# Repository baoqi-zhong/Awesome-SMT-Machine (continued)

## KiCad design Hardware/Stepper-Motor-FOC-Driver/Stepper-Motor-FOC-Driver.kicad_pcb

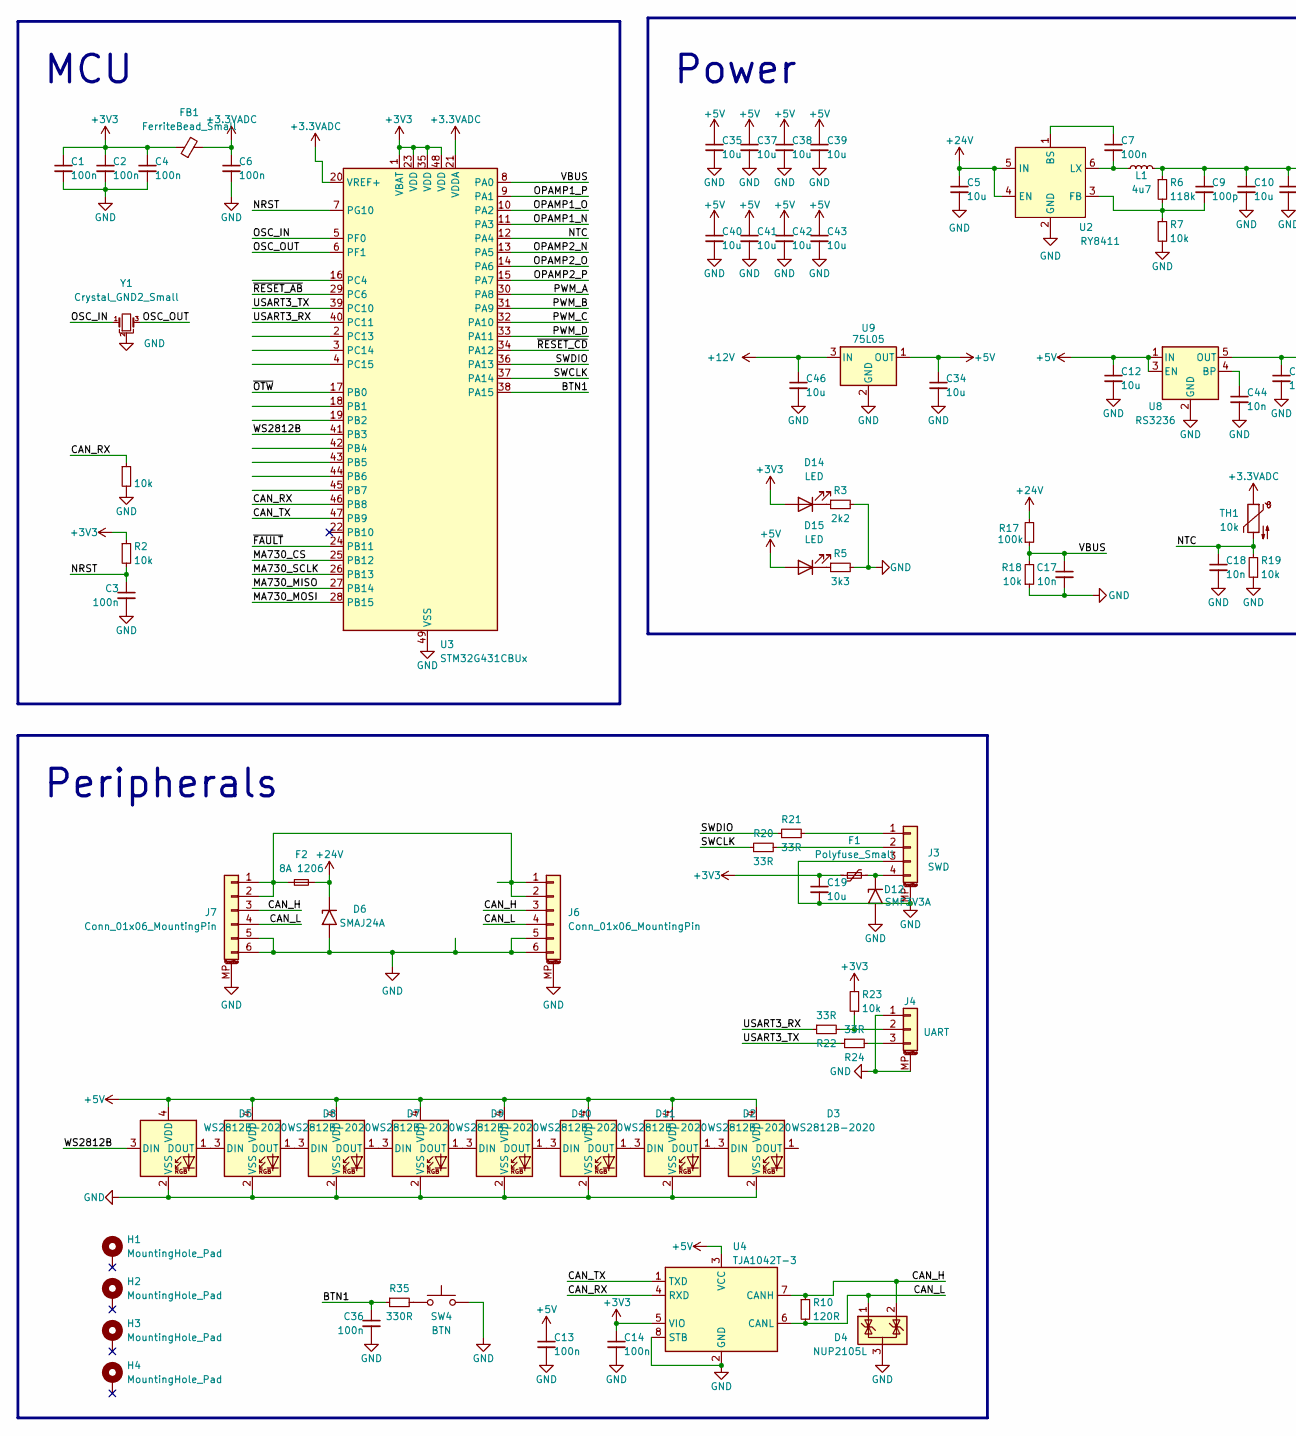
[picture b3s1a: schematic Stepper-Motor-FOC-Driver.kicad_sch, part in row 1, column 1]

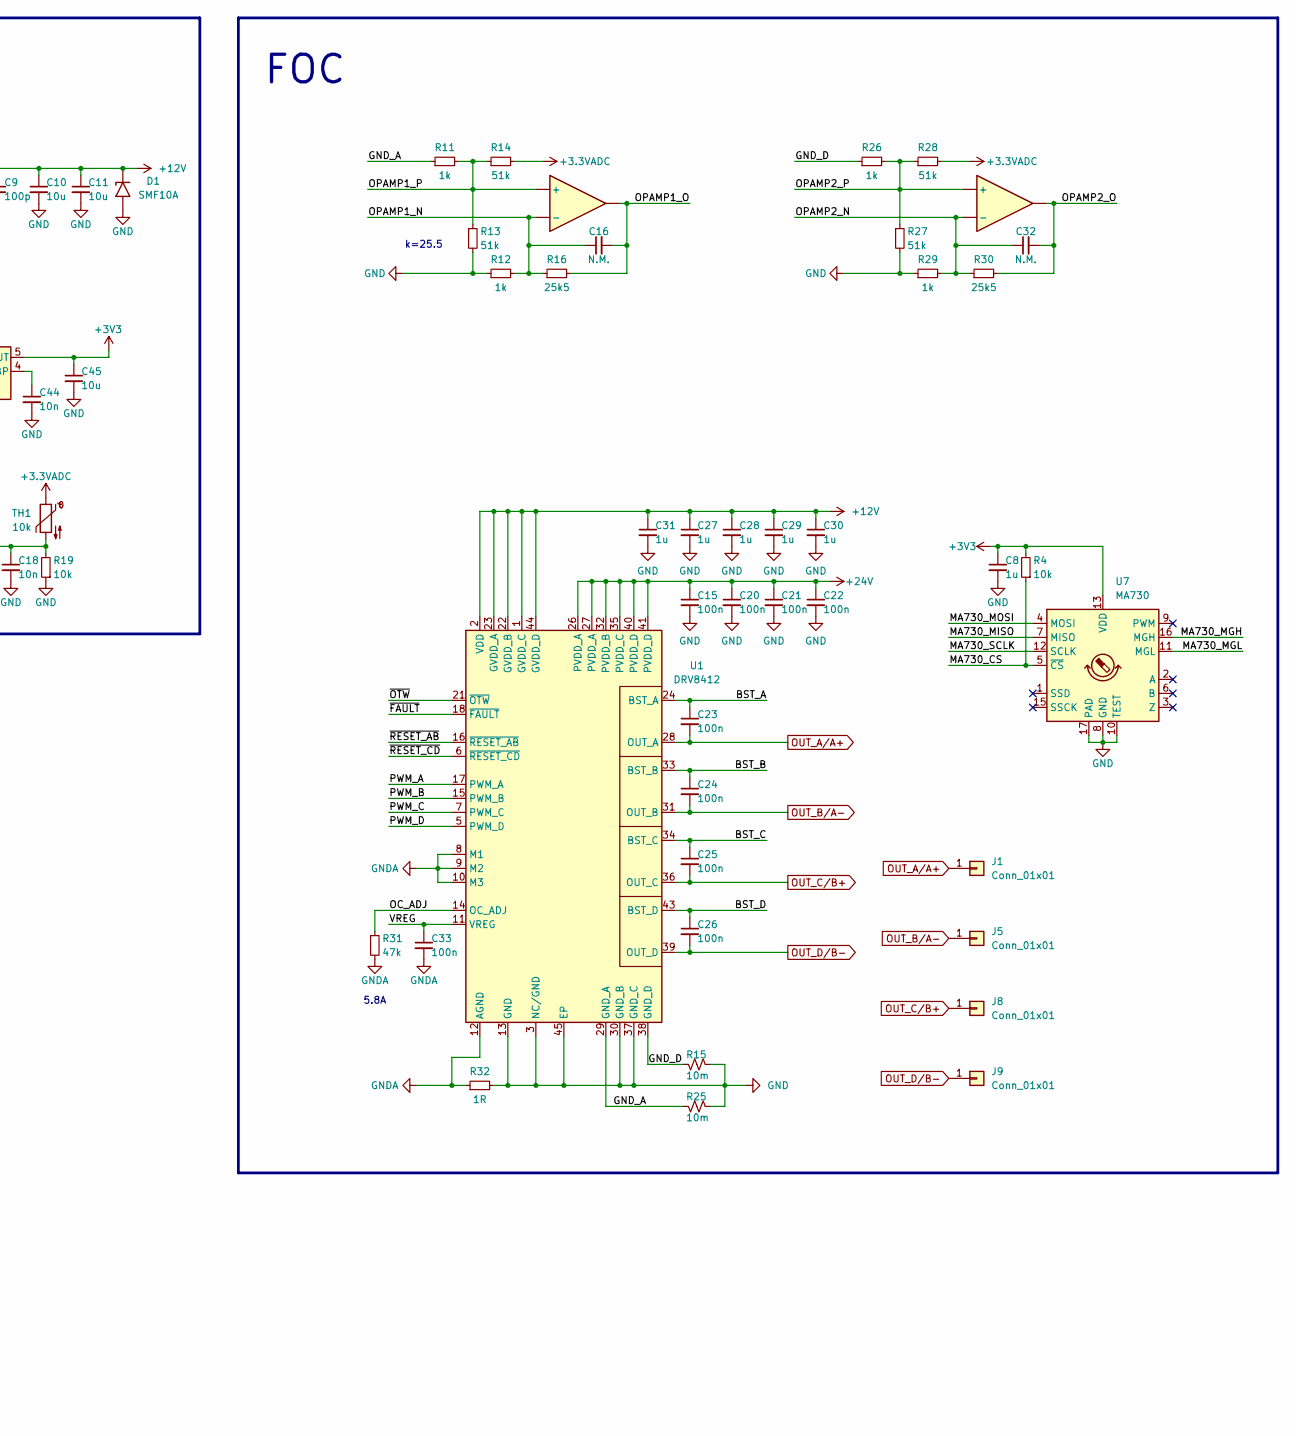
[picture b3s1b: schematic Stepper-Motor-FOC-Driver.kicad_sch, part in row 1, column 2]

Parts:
C1, C2, C3, C4, C6, C7, C13, C14, C15, C20, C21, C22, C23, C24, C25, C26, C33, C36: 100n; C_0603_1608Metric
C5, C10, C11: 10u; C_1206_3216Metric
C8, C27, C28, C29, C30, C31: 1u; C_0603_1608Metric
C9: 100p; C_0603_1608Metric
C12, C19, C34, C35, C37, C38, C39, C40, C41, C42, C43, C45, C46: 10u; C_0603_1608Metric
C16, C32: N.M.; C_0603_1608Metric
C17, C18, C44: 10n; C_0603_1608Metric
D1: SMF10A; D_SMF
D2, D3, D5, D7, D8, D9, D10, D11: WS2812B-2020; LED_WS2812B-2020_PLCC4_2.0x2.0mm
D4: NUP2105L; SOT-23
D6: SMAJ24A; D_SMA
D12: SMF3V3A; D_SMF
D14, D15: LED; LED_0603_1608Metric
F1: Polyfuse_Small; Fuse_1206_3216Metric
F2: 8A 1206; Fuse_1206_3216Metric
FB1: FerriteBead_Small; L_0603_1608Metric
H1, H2, H3, H4: MountingHole_Pad; MountingHole_3.2mm_M3_DIN965_Pad
J1, J5, J8, J9: Conn_01x01; TestPoint_Pad_3.0x3.0mm
J3: SWD; Molex_PicoBlade_53047-0410_1x04_P1.25mm_Vertical
J4: UART; JST_GH_SM03B-GHS-TB_1x03-1MP_P1.25mm_Horizontal
J6, J7: Conn_01x06_MountingPin; JST_PH_S6B-PH-K_1x06_P2.00mm_Horizontal
L1: 4u7; L_Sunlord_MWSA0402S
R1, R2, R4, R7, R18, R19, R23: 10k; R_0603_1608Metric
R3: 2k2; R_0603_1608Metric
R5: 3k3; R_0603_1608Metric
R6: 118k; R_0603_1608Metric
R10: 120R; R_0603_1608Metric
R11, R12, R26, R29: 1k; R_0603_1608Metric
R13, R14, R27, R28: 51k; R_0603_1608Metric
R15, R25: 10m; R_1206_3216Metric
R16, R30: 25k5; R_0603_1608Metric
R17: 100k; R_0603_1608Metric
R20, R21, R22, R24: 33R; R_0603_1608Metric
R31: 47k; R_0603_1608Metric
R32: 1R; R_0603_1608Metric
R35: 330R; R_0603_1608Metric
SW4: BTN; SW_SPST_PTS810
TH1: 10k; TestPoint_2Pads_Pitch2.54mm_Drill0.8mm
U1: DRV8412; HTSSOP-44-1EP_6.1x14mm_P0.635mm_EP5.2x14mm_Mask4.31x8.26mm
U2: RY8411; SOT-23-6
U3: STM32G431CBUx; QFN-48-1EP_7x7mm_P0.5mm_EP5.6x5.6mm
U4: TJA1042T-3; SOIC-8_3.9x4.9mm_P1.27mm
U5, U6: type="X" model="OPAMP" lib=""
U7: MA730; QFN-16-1EP_3x3mm_P0.5mm_EP1.75x1.75mm
U8: RS3236; SOT-23-5
U9: 75L05; SOT-89-3
Y1: Crystal_GND2_Small; Resonator_SMD_Murata_CSTxExxV-3Pin_3.0x1.1mm

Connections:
+3.3VADC: C6.1, FB1.2, R14.2, R28.2, TH1.1, U3.20 (VREF+), U3.21 (VDDA)
+3V3: C1.1, C2.1, C4.1, C8.1, C14.1, C19.1, C45.1, D14.2 (A), F1.1, FB1.1, R2.1, R4.2, R23.2, U3.1 (VBAT), U3.23 (VDD), U3.35 (VDD), U3.48 (VDD), U4.5 (VIO), U7.13 (VDD), U8.5 (OUT)
+5V: C12.1, C13.1, C34.1, C35.1, C37.1, C38.1, C39.1, C40.1, C41.1, C42.1, C43.1, D2.4 (VDD), D3.4 (VDD), D5.4 (VDD), D7.4 (VDD), D8.4 (VDD), D9.4 (VDD), D10.4 (VDD), D11.4 (VDD), D15.2 (A), U4.3 (VCC), U8.1 (IN), U8.3 (EN), U9.1 (OUT)
+12V: C9.1, C10.1, C11.1, C27.1, C28.1, C29.1, C30.1, C31.1, C46.1, D1.1 (A1), L1.2, R6.1, U1.1 (GVDD_C), U1.2 (VDD), U1.22 (GVDD_B), U1.23 (GVDD_A), U1.44 (GVDD_D), U9.3 (IN)
+24V: C5.1, C15.1, C20.1, C21.1, C22.1, D6.1 (A1), F2.2, R17.2, U1.26 (PVDD_A), U1.27 (PVDD_A), U1.32 (PVDD_B), U1.35 (PVDD_C), U1.40 (PVDD_D), U1.41 (PVDD_D), U2.4 (EN), U2.5 (IN)
/BST_A: C23.1, U1.24 (BST_A)
/BST_B: C24.1, U1.33 (BST_B)
/BST_C: C25.1, U1.34 (BST_C)
/BST_D: C26.1, U1.43 (BST_D)
/BTN1: C36.1, R35.1, U3.38 (PA15)
/CAN_H: D4.2 (K), J6.3, J7.3, R10.1, U4.7 (CANH)
/CAN_L: D4.1 (K), J6.4, J7.4, R10.2, U4.6 (CANL)
/CAN_RX: R1.1, U3.46 (PB8), U4.4 (RXD)
/CAN_TX: U3.47 (PB9), U4.1 (TXD)
/GND_A: R11.1, R25.2, U1.29 (GND_A)
/GND_D: R15.2, R26.1, U1.38 (GND_D)
/MA730_CS: R4.1, U3.25 (PB12), U7.5 (~CS)
/MA730_MGH: U7.16 (MGH)
/MA730_MGL: U7.11 (MGL)
/MA730_MISO: U3.27 (PB14), U7.7 (MISO)
/MA730_MOSI: U3.28 (PB15), U7.4 (MOSI)
/MA730_SCLK: U3.26 (PB13), U7.12 (SCLK)
/NRST: C3.1, R2.2, U3.7 (PG10)
/NTC: C18.1, R19.2, TH1.2, U3.12 (PA4)
/OC_ADJ: R31.1, U1.14 (OC_ADJ)
/OPAMP1_N: C16.1, R12.2, R16.1, U3.11 (PA3), U5.
/OPAMP1_O: C16.2, R16.2, U3.10 (PA2), U5.
/OPAMP1_P: R11.2, R13.1, R14.1, U3.9 (PA1), U5.
/OPAMP2_N: C32.1, R29.2, R30.1, U3.13 (PA5), U6.
/OPAMP2_O: C32.2, R30.2, U3.14 (PA6), U6.
/OPAMP2_P: R26.2, R27.1, R28.1, U3.15 (PA7), U6.
/OSC_IN: U3.5 (PF0), Y1.1
/OSC_OUT: U3.6 (PF1), Y1.3
/PWM_A: U1.17 (PWM_A), U3.30 (PA8)
/PWM_B: U1.15 (PWM_B), U3.31 (PA9)
/PWM_C: U1.7 (PWM_C), U3.32 (PA10)
/PWM_D: U1.5 (PWM_D), U3.33 (PA11)
/SWCLK: R20.1, U3.37 (PA14)
/SWDIO: R21.1, U3.36 (PA13)
/USART3_RX: R22.1, U3.40 (PC11)
/USART3_TX: R24.1, U3.39 (PC10)
/VBUS: C17.1, R17.1, R18.2, U3.8 (PA0)
/VREG: C33.1, U1.11 (VREG)
/WS2812B: D5.3 (DIN), U3.41 (PB3)
/~FAULT: U1.18 (~FAULT), U3.24 (PB11)
/~OTW: U1.21 (~OTW), U3.17 (PB0)
/~RESET_AB: U1.16 (~RESET_AB), U3.29 (PC6)
/~RESET_CD: U1.6 (~RESET_CD), U3.34 (PA12)
GND: C1.2, C2.2, C3.2, C4.2, C5.2, C6.2, C8.2, C10.2, C11.2, C12.2, C13.2, C14.2, C15.2, C17.2, C18.2, C19.2, C20.2, C21.2, C22.2, C27.2, C28.2, C29.2, C30.2, C31.2, C34.2, C35.2, C36.2, C37.2, C38.2, C39.2, C40.2, C41.2, C42.2, C43.2, C44.2, C45.2, C46.2, D1.2 (A2), D2.2 (VSS), D3.2 (VSS), D4.3 (A), D5.2 (VSS), D6.2 (A2), D7.2 (VSS), D8.2 (VSS), D9.2 (VSS), D10.2 (VSS), D11.2 (VSS), D12.2 (A2), J3.3, J3.MP (MountPin), J4.1, J4.MP (MountPin), J6.5, J6.6, J6.MP (MountPin), J7.5, J7.6, J7.MP (MountPin), R1.2, R3.2, R5.2, R7.2, R12.1, R13.2, R15.1, R18.1, R19.1, R25.1, R27.2, R29.1, R32.2, SW4.2, U1.3 (NC/GND), U1.4 (NC/GND), U1.13 (GND), U1.19 (NC/GND), U1.20 (NC/GND), U1.25 (NC/GND), U1.30 (GND_B), U1.37 (GND_C), U1.42 (NC/GND), U1.45 (EP), U2.2 (GND), U3.49 (VSS), U4.2 (GND), U4.8 (STB), U7.8 (GND), U7.10 (TEST), U7.17 (PAD), U8.2 (GND), U9.2 (GND), Y1.2
GNDA: C33.2, R31.2, R32.1, U1.8 (M1), U1.9 (M2), U1.10 (M3), U1.12 (AGND)
unnamed: D2.1 (DOUT), D3.3 (DIN)
unnamed: D5.1 (DOUT), D8.3 (DIN)
unnamed: D7.3 (DIN), D8.1 (DOUT)
unnamed: D7.1 (DOUT), D9.3 (DIN)
unnamed: D9.1 (DOUT), D10.3 (DIN)
unnamed: D10.1 (DOUT), D11.3 (DIN)
unnamed: D2.3 (DIN), D11.1 (DOUT)
unnamed: D12.1 (A1), F1.2, J3.4
unnamed: D14.1 (K), R3.1
unnamed: D15.1 (K), R5.1
unnamed: J3.1, R21.2
unnamed: J3.2, R20.2
unnamed: J4.2, R22.2, R23.1
unnamed: J4.3, R24.2
unnamed: F2.1, J6.1, J6.2, J7.1, J7.2
unnamed: R35.2, SW4.1
unnamed: C7.1, U2.1 (BS)
unnamed: C9.2, R6.2, R7.1, U2.3 (FB)
unnamed: C7.2, L1.1, U2.6 (LX)
unnamed: C44.1, U8.4 (BP)
OUT_A/A+: C23.2, J1.1, U1.28 (OUT_A)
OUT_B/A-: C24.2, J5.1, U1.31 (OUT_B)
OUT_C/B+: C25.2, J8.1, U1.36 (OUT_C)
OUT_D/B-: C26.2, J9.1, U1.39 (OUT_D)

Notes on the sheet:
5.8A
Peripherals
FOC
MCU
Power
k=25.5

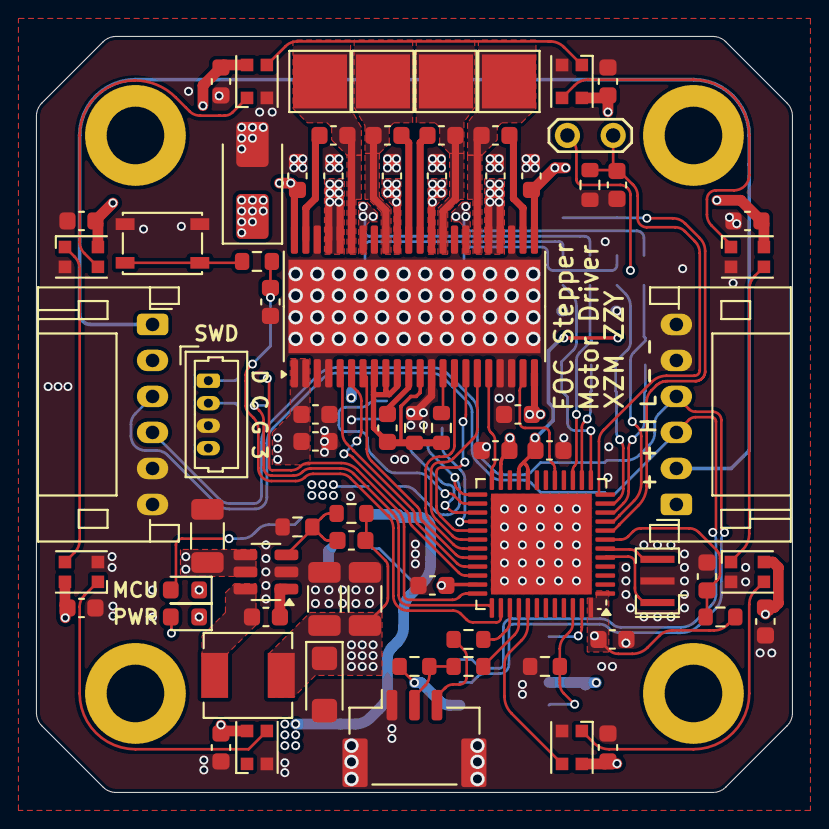
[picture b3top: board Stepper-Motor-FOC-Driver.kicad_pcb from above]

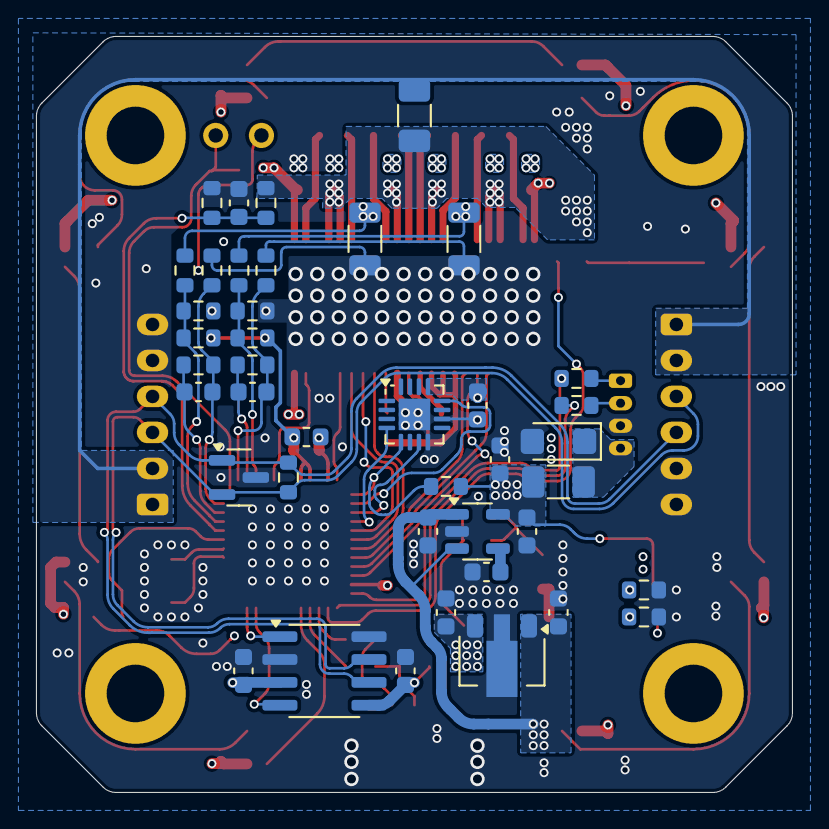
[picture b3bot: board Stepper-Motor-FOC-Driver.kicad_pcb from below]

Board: 4 copper layers, 42.0 x 42.0 mm, 117 parts (41 on the bottom side), 72 nets.

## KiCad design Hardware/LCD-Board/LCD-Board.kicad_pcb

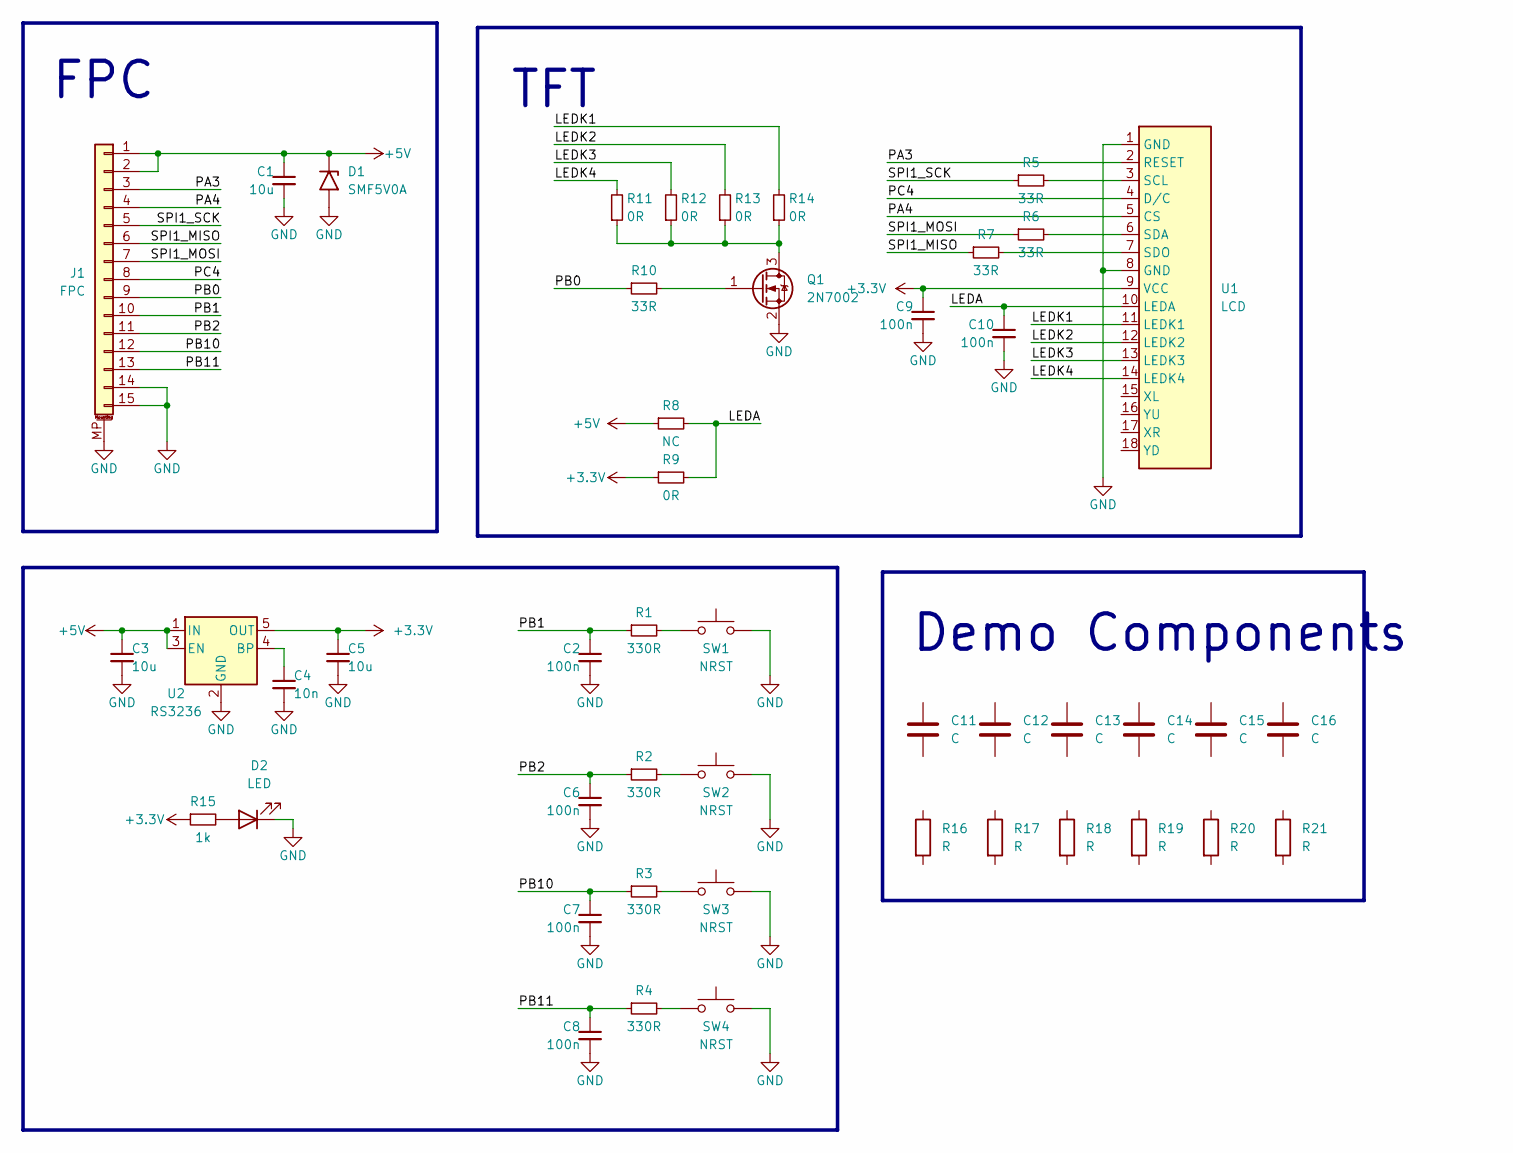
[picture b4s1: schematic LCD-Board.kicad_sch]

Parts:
C1, C3, C5: 10u; C_0603_1608Metric
C2, C6, C7, C8, C9, C10: 100n; C_0603_1608Metric
C4: 10n; C_0603_1608Metric
C11, C12, C13, C14, C15, C16: C; C_0805_2012Metric
D1: SMF5V0A; D_SMF
D2: LED; LED_0603_1608Metric
J1: FPC; TE_1-84952-5_1x15-1MP_P1.0mm_Horizontal
Q1: 2N7002; SOT-23
R1, R2, R3, R4: 330R; R_0603_1608Metric
R5, R6, R7, R10: 33R; R_0603_1608Metric
R8: NC; R_0603_1608Metric
R9, R11, R12, R13, R14: 0R; R_0603_1608Metric
R15: 1k; R_0603_1608Metric
R16, R17, R18, R19, R20, R21: R; R_0805_2012Metric
SW1, SW2, SW3, SW4: NRST; SW_SPST_PTS810
U1: LCD; Display_LCD_TFT_ST7789
U2: RS3236; SOT-23-5

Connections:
+3.3V: C5.1, C9.1, R9.1, R15.1, U1.9 (VCC), U2.5 (OUT)
+5V: C1.1, C3.1, D1.1 (A1), J1.1, J1.2, R8.1, U2.1 (IN), U2.3 (EN)
/LEDA: C10.1, R8.2, R9.2, U1.10 (LEDA)
/LEDK1: R14.2, U1.11 (LEDK1)
/LEDK2: R13.2, U1.12 (LEDK2)
/LEDK3: R12.2, U1.13 (LEDK3)
/LEDK4: R11.2, U1.14 (LEDK4)
/PA3: J1.3, U1.2 (RESET)
/PA4: J1.4, U1.5 (CS)
/PB0: J1.9, R10.1
/PB1: C2.1, J1.10, R1.1
/PB2: C6.1, J1.11, R2.1
/PB10: C7.1, J1.12, R3.1
/PB11: C8.1, J1.13, R4.1
/PC4: J1.8, U1.4 (D/C)
/SPI1_MISO: J1.6, R7.1
/SPI1_MOSI: J1.7, R6.1
/SPI1_SCK: J1.5, R5.1
GND: C1.2, C2.2, C3.2, C4.2, C5.2, C6.2, C7.2, C8.2, C9.2, C10.2, D1.2 (A2), D2.1 (K), J1.14, J1.15, J1.MP (MountPin), Q1.2 (S), SW1.2, SW2.2, SW3.2, SW4.2, U1.1 (GND), U1.8 (GND), U2.2 (GND)
unnamed: D2.2 (A), R15.2
unnamed: Q1.3 (D), R11.1, R12.1, R13.1, R14.1
unnamed: Q1.1 (G), R10.2
unnamed: R1.2, SW1.1
unnamed: R2.2, SW2.1
unnamed: R3.2, SW3.1
unnamed: R4.2, SW4.1
unnamed: R5.2, U1.3 (SCL)
unnamed: R6.2, U1.6 (SDA)
unnamed: R7.2, U1.7 (SDO)
unnamed: C4.1, U2.4 (BP)

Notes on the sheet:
TFT
Demo Components
FPC

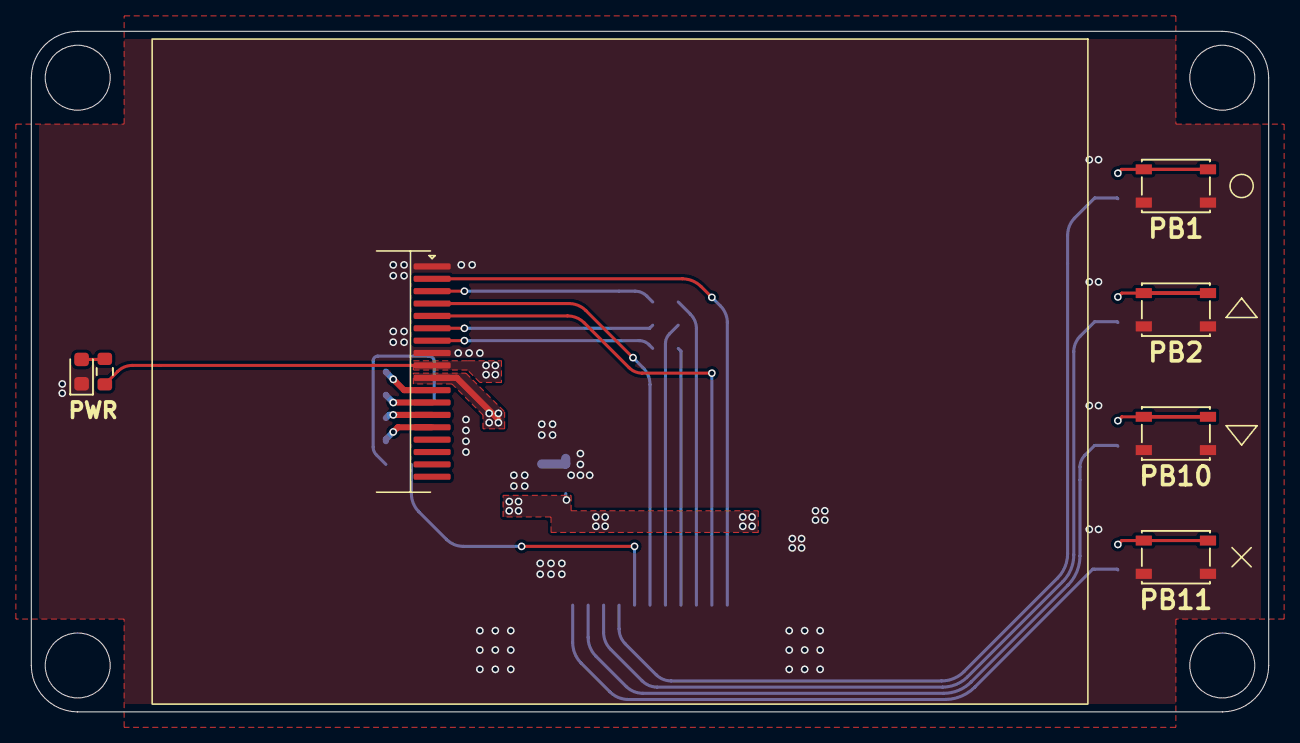
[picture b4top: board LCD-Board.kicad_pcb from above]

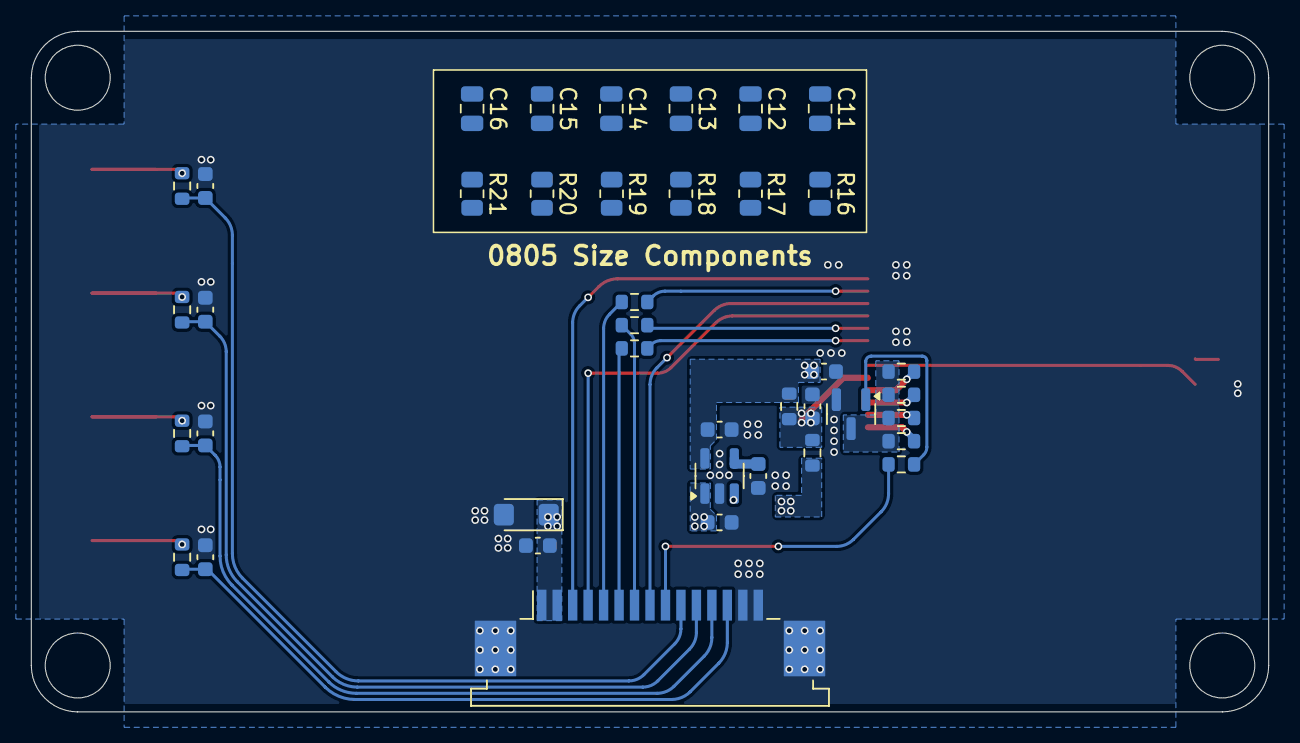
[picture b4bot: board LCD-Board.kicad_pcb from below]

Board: 2 copper layers, 80.0 x 44.0 mm, 47 parts (40 on the bottom side), 30 nets.

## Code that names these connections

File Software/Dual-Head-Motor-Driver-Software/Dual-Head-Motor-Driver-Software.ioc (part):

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Mcu.Name=STM32G431C(6-8-B)Ux
Mcu.Package=UFQFPN48
Mcu.UserName=STM32G431CBUx
PA0.GPIOParameters=GPIO_PuPd,GPIO_Label
PA0.GPIO_Label=GPIO1
PA0.GPIO_PuPd=GPIO_PULLUP
PA0.Signal=GPIO_Input
PA1.Mode=PGA Connected
PA1.Signal=OPAMP1_VINP
PA10.Signal=S_TIM1_CH3
PA11.Mode=FDCAN_Activate
PA11.Signal=FDCAN1_RX
PA12.Mode=FDCAN_Activate
PA12.Signal=FDCAN1_TX
PA13.Mode=Serial_Wire
PA13.Signal=SYS_JTMS-SWDIO
PA14.Mode=Serial_Wire
PA14.Signal=SYS_JTCK-SWCLK
PA15.Signal=S_TIM2_CH1
PA2.Signal=SharedAnalog_PA2
PA3.Mode=PGA Connected
PA3.Signal=OPAMP1_VINM0
PA4.GPIOParameters=GPIO_PuPd,GPIO_Label
PA4.GPIO_Label=MICRO_SW
PA4.GPIO_PuPd=GPIO_PULLUP
PA4.Signal=GPIO_Input
PA5.Mode=PGA Connected
PA5.Signal=OPAMP2_VINM0
PA6.Signal=SharedAnalog_PA6
PA7.Mode=PGA Connected
PA7.Signal=OPAMP2_VINP
PA8.Signal=S_TIM1_CH1
PA9.Signal=S_TIM1_CH2
PB0.Mode=PGA Connected
PB0.Signal=OPAMP3_VINP
PB1.Signal=SharedAnalog_PB1
PB11.GPIOParameters=GPIO_Label
PB11.GPIO_Label=VBUS_SENSE
PB11.Signal=SharedAnalog_PB11
PB12.GPIOParameters=GPIO_PuPd,GPIO_Label
PB12.GPIO_Label=GPIO2
PB12.GPIO_PuPd=GPIO_PULLUP
PB12.Signal=GPIO_Input
PB13.GPIOParameters=GPIO_Speed,GPIO_Label
PB13.GPIO_Label=VALVE_1
PB13.GPIO_Speed=GPIO_SPEED_FREQ_VERY_HIGH
PB13.Signal=GPIO_Output
PB2.Mode=PGA Connected
PB2.Signal=OPAMP3_VINM0
PB3.Signal=S_TIM2_CH2
PB4.GPIOParameters=GPIO_PuPd,GPIO_Label
PB4.GPIO_Label=M2_nFAULT
PB4.GPIO_PuPd=GPIO_PULLUP
PB4.Signal=GPIO_Input
PB5.GPIOParameters=GPIO_PuPd,GPIO_Label
PB5.GPIO_Label=M3_nFAULT
PB5.GPIO_PuPd=GPIO_PULLUP
PB5.Signal=GPIO_Input
PB6.Signal=S_TIM4_CH1
PB7.Signal=S_TIM4_CH2
PB8-BOOT0.Signal=S_TIM4_CH3
PB9.Signal=S_TIM4_CH4
PC10.Mode=PWM Generation1 CH1N
PC10.Signal=TIM8_CH1N
PC11.Mode=PWM Generation2 CH2N
PC11.Signal=TIM8_CH2N
PC13.GPIOParameters=GPIO_PuPd,GPIO_Label
PC13.GPIO_Label=M1_nFAULT
PC13.GPIO_PuPd=GPIO_PULLUP
PC13.Signal=GPIO_Input
PC14-OSC32_IN.GPIOParameters=GPIO_Label
PC14-OSC32_IN.GPIO_Label=VALVE_2
PC14-OSC32_IN.Signal=GPIO_Output
PC15-OSC32_OUT.GPIOParameters=GPIO_PuPd,GPIO_Label
PC15-OSC32_OUT.GPIO_Label=GPIO3
PC15-OSC32_OUT.GPIO_PuPd=GPIO_PULLUP
PC15-OSC32_OUT.Signal=GPIO_Input
PC6.Signal=S_TIM3_CH1
PF0-OSC_IN.Mode=HSE-External-Oscillator
PF0-OSC_IN.Signal=RCC_OSC_IN
PF1-OSC_OUT.Mode=HSE-External-Oscillator
PF1-OSC_OUT.Signal=RCC_OSC_OUT
RCC.HSE_VALUE=8000000
RCC.SYSCLKFreq_VALUE=170000000
RCC.SYSCLKSource=RCC_SYSCLKSOURCE_PLLCLK
board=custom

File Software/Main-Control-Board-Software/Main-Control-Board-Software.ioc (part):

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Mcu.Name=STM32G431C(6-8-B)Ux
Mcu.Package=UFQFPN48
Mcu.UserName=STM32G431CBUx
PA0.GPIOParameters=GPIO_Label
PA0.GPIO_Label=WS2812_TIM
PA0.Signal=S_TIM2_CH1
PA1.GPIOParameters=PinState,GPIO_PuPd,GPIO_Label
PA1.GPIO_Label=PUMP
PA1.GPIO_PuPd=GPIO_PULLDOWN
PA1.PinState=GPIO_PIN_RESET
PA1.Signal=GPIO_Output
PA10.GPIOParameters=GPIO_Label
PA10.GPIO_Label=APM_ADR
PA10.Signal=GPIO_Input
PA11.Mode=FDCAN_Activate
PA11.Signal=FDCAN1_RX
PA12.Mode=FDCAN_Activate
PA12.Signal=FDCAN1_TX
PA13.Mode=Serial_Wire
PA13.Signal=SYS_JTMS-SWDIO
PA14.Mode=Serial_Wire
PA14.Signal=SYS_JTCK-SWCLK
PA2.GPIOParameters=GPIO_Label
PA2.GPIO_Label=SERVO_TIM
PA2.Signal=S_TIM15_CH1
PA3.GPIOParameters=GPIO_Speed,PinState,GPIO_Label
PA3.GPIO_Label=LCD_RST
PA3.GPIO_Speed=GPIO_SPEED_FREQ_VERY_HIGH
PA3.PinState=GPIO_PIN_RESET
PA3.Signal=GPIO_Output
PA4.GPIOParameters=GPIO_Speed,PinState,GPIO_Label
PA4.GPIO_Label=LCD_CS
PA4.GPIO_Speed=GPIO_SPEED_FREQ_VERY_HIGH
PA4.PinState=GPIO_PIN_SET
PA4.Signal=GPIO_Output
PA5.GPIOParameters=GPIO_Speed,GPIO_PuPd
PA5.GPIO_PuPd=GPIO_PULLDOWN
PA5.GPIO_Speed=GPIO_SPEED_FREQ_VERY_HIGH
PA5.Mode=Full_Duplex_Master
PA5.Signal=SPI1_SCK
PA6.GPIOParameters=GPIO_Speed,GPIO_PuPd
PA6.GPIO_PuPd=GPIO_PULLUP
PA6.GPIO_Speed=GPIO_SPEED_FREQ_VERY_HIGH
PA6.Mode=Full_Duplex_Master
PA6.Signal=SPI1_MISO
PA7.GPIOParameters=GPIO_Speed,GPIO_PuPd
PA7.GPIO_PuPd=GPIO_PULLUP
PA7.GPIO_Speed=GPIO_SPEED_FREQ_VERY_HIGH
PA7.Mode=Full_Duplex_Master
PA7.Signal=SPI1_MOSI
PA8.GPIOParameters=GPIO_Speed
PA8.GPIO_Speed=GPIO_SPEED_FREQ_MEDIUM
PA8.Mode=I2C
PA8.Signal=I2C2_SDA
PA9.GPIOParameters=GPIO_Speed
PA9.GPIO_Speed=GPIO_SPEED_FREQ_MEDIUM
PA9.Mode=I2C
PA9.Signal=I2C2_SCL
PB0.GPIOParameters=GPIO_Speed,PinState,GPIO_Label
PB0.GPIO_Label=LCD_BG
PB0.GPIO_Speed=GPIO_SPEED_FREQ_HIGH
PB0.PinState=GPIO_PIN_RESET
PB0.Signal=GPIO_Output
PB12.GPIOParameters=GPIO_Speed
PB12.GPIO_Speed=GPIO_SPEED_FREQ_HIGH
PB12.Mode=Half_Duplex_Master
PB12.Signal=I2S2_WS
PB13.GPIOParameters=GPIO_Speed
PB13.GPIO_Speed=GPIO_SPEED_FREQ_HIGH
PB13.Mode=Half_Duplex_Master
PB13.Signal=I2S2_CK
PB14.GPIOParameters=GPIO_PuPd,GPIO_Label,GPIO_ModeDefaultOutputPP
PB14.GPIO_Label=LED_ACT
PB14.GPIO_ModeDefaultOutputPP=GPIO_MODE_OUTPUT_OD
PB14.GPIO_PuPd=GPIO_NOPULL
PB14.Signal=GPIO_Output
PB15.GPIOParameters=GPIO_Speed
PB15.GPIO_Speed=GPIO_SPEED_FREQ_HIGH
PB15.Mode=Half_Duplex_Master
PB15.Signal=I2S2_SD
PB7.GPIOParameters=GPIO_Pu
PB7.GPIO_Pu=GPIO_PULLUP
PB7.Mode=I2C
PB7.Signal=I2C1_SDA
PB8-BOOT0.GPIOParameters=GPIO_Pu
PB8-BOOT0.GPIO_Pu=GPIO_PULLUP
PB8-BOOT0.Mode=I2C
PB8-BOOT0.Signal=I2C1_SCL
PB9.GPIOParameters=PinState,GPIO_Label
PB9.GPIO_Label=PSTOP
PB9.PinState=GPIO_PIN_SET
PB9.Signal=GPIO_Output
PC10.Mode=Asynchronous
PC10.Signal=USART3_TX
PC11.Mode=Asynchronous
PC11.Signal=USART3_RX
PC13.GPIOParameters=GPIO_PuPd,GPIO_Label
PC13.GPIO_Label=BUTTON0
PC13.GPIO_PuPd=GPIO_PULLUP
PC13.Signal=GPIO_Input
PC14-OSC32_IN.GPIOParameters=GPIO_PuPd,GPIO_Label
PC14-OSC32_IN.GPIO_Label=TriggerY
PC14-OSC32_IN.GPIO_PuPd=GPIO_PULLUP
PC14-OSC32_IN.Signal=GPIO_Input
PC4.GPIOParameters=GPIO_Speed,GPIO_Label
PC4.GPIO_Label=LCD_DC
PC4.GPIO_Speed=GPIO_SPEED_FREQ_VERY_HIGH
PC4.Signal=GPIO_Output
PC6.GPIOParameters=GPIO_Speed,PinState,GPIO_Label
PC6.GPIO_Label=APM_PDN
PC6.GPIO_Speed=GPIO_SPEED_FREQ_MEDIUM
PC6.PinState=GPIO_PIN_RESET
PC6.Signal=GPIO_Output
PF0-OSC_IN.Mode=HSE-External-Oscillator
PF0-OSC_IN.Signal=RCC_OSC_IN
PF1-OSC_OUT.Mode=HSE-External-Oscillator
PF1-OSC_OUT.Signal=RCC_OSC_OUT
RCC.HSE_VALUE=25000000
RCC.SYSCLKFreq_VALUE=170000000
RCC.SYSCLKSource=RCC_SYSCLKSOURCE_PLLCLK
board=custom

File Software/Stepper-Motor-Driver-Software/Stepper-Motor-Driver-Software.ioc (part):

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Mcu.Name=STM32G431C(6-8-B)Ux
Mcu.Package=UFQFPN48
Mcu.UserName=STM32G431CBUx
PA0.GPIOParameters=GPIO_Label
PA0.GPIO_Label=VBUS
PA0.Mode=IN1-Single-Ended
PA0.Signal=ADC1_IN1
PA1.Mode=Standalone
PA1.Signal=OPAMP1_VINP
PA10.GPIOParameters=GPIO_Speed
PA10.GPIO_Speed=GPIO_SPEED_FREQ_VERY_HIGH
PA10.Signal=S_TIM1_CH3
PA11.GPIOParameters=GPIO_Speed
PA11.GPIO_Speed=GPIO_SPEED_FREQ_VERY_HIGH
PA11.Signal=S_TIM1_CH4
PA12.GPIOParameters=GPIO_Label
PA12.GPIO_Label=NRST_CD
PA12.Signal=GPIO_Output
PA13.Mode=Serial_Wire
PA13.Signal=SYS_JTMS-SWDIO
PA14.Mode=Serial_Wire
PA14.Signal=SYS_JTCK-SWCLK
PA2.Signal=SharedAnalog_PA2
PA3.Mode=Standalone
PA3.Signal=OPAMP1_VINM
PA4.GPIOParameters=GPIO_Label
PA4.GPIO_Label=NTC
PA4.Mode=IN17-Single-Ended
PA4.Signal=ADC2_IN17
PA5.Mode=Standalone
PA5.Signal=OPAMP2_VINM
PA6.Signal=SharedAnalog_PA6
PA7.Mode=Standalone
PA7.Signal=OPAMP2_VINP
PA8.GPIOParameters=GPIO_Speed
PA8.GPIO_Speed=GPIO_SPEED_FREQ_VERY_HIGH
PA8.Signal=S_TIM1_CH1
PA9.GPIOParameters=GPIO_Speed
PA9.GPIO_Speed=GPIO_SPEED_FREQ_VERY_HIGH
PA9.Signal=S_TIM1_CH2
PB0.GPIOParameters=GPIO_Label
PB0.GPIO_Label=nOTW
PB0.Signal=GPIO_Input
PB11.GPIOParameters=GPIO_Label
PB11.GPIO_Label=nFAULT
PB11.Signal=GPIO_Input
PB12.Mode=NSS_Signal_Hard_Output
PB12.Signal=SPI2_NSS
PB13.Mode=Full_Duplex_Master
PB13.Signal=SPI2_SCK
PB14.Mode=Full_Duplex_Master
PB14.Signal=SPI2_MISO
PB15.Mode=Full_Duplex_Master
PB15.Signal=SPI2_MOSI
PB3.GPIOParameters=GPIO_Label
PB3.GPIO_Label=WS2812
PB3.Signal=S_TIM2_CH2
PB8-BOOT0.Mode=FDCAN_Activate
PB8-BOOT0.Signal=FDCAN1_RX
PB9.Mode=FDCAN_Activate
PB9.Signal=FDCAN1_TX
PC10.GPIOParameters=GPIO_Speed
PC10.GPIO_Speed=GPIO_SPEED_FREQ_VERY_HIGH
PC10.Signal=GPIO_Output
PC11.GPIOParameters=GPIO_Label
PC11.GPIO_Label=MicroSwitch
PC11.Signal=GPIO_Input
PC6.GPIOParameters=GPIO_Label
PC6.GPIO_Label=NRST_AB
PC6.Signal=GPIO_Output
PF0-OSC_IN.Mode=HSE-External-Oscillator
PF0-OSC_IN.Signal=RCC_OSC_IN
PF1-OSC_OUT.Mode=HSE-External-Oscillator
PF1-OSC_OUT.Signal=RCC_OSC_OUT
RCC.HSE_VALUE=8000000
RCC.SYSCLKFreq_VALUE=170000000
RCC.SYSCLKSource=RCC_SYSCLKSOURCE_PLLCLK
board=custom

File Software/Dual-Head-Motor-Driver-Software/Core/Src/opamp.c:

/* USER CODE BEGIN Header */
/**
  ******************************************************************************
  * @file    opamp.c
  * @brief   This file provides code for the configuration
  *          of the OPAMP instances.
  ******************************************************************************
  * @attention
  *
  * Copyright (c) 2024 STMicroelectronics.
  * All rights reserved.
  *
  * This software is licensed under terms that can be found in the LICENSE file
  * in the root directory of this software component.
  * If no LICENSE file comes with this software, it is provided AS-IS.
  *
  ******************************************************************************
  */
/* USER CODE END Header */
/* Includes ------------------------------------------------------------------*/
#include "opamp.h"

/* USER CODE BEGIN 0 */

/* USER CODE END 0 */

OPAMP_HandleTypeDef hopamp1;
OPAMP_HandleTypeDef hopamp2;
OPAMP_HandleTypeDef hopamp3;

/* OPAMP1 init function */
void MX_OPAMP1_Init(void)
{

  /* USER CODE BEGIN OPAMP1_Init 0 */

  /* USER CODE END OPAMP1_Init 0 */

  /* USER CODE BEGIN OPAMP1_Init 1 */

  /* USER CODE END OPAMP1_Init 1 */
  hopamp1.Instance = OPAMP1;
  hopamp1.Init.PowerMode = OPAMP_POWERMODE_NORMALSPEED;
  hopamp1.Init.Mode = OPAMP_PGA_MODE;
  hopamp1.Init.NonInvertingInput = OPAMP_NONINVERTINGINPUT_IO0;
  hopamp1.Init.InternalOutput = DISABLE;
  hopamp1.Init.TimerControlledMuxmode = OPAMP_TIMERCONTROLLEDMUXMODE_DISABLE;
  hopamp1.Init.PgaConnect = OPAMP_PGA_CONNECT_INVERTINGINPUT_IO0;
  hopamp1.Init.PgaGain = OPAMP_PGA_GAIN_16_OR_MINUS_15;
  hopamp1.Init.UserTrimming = OPAMP_TRIMMING_FACTORY;
  if (HAL_OPAMP_Init(&hopamp1) != HAL_OK)
  {
    Error_Handler();
  }
  /* USER CODE BEGIN OPAMP1_Init 2 */

  /* USER CODE END OPAMP1_Init 2 */

}
/* OPAMP2 init function */
void MX_OPAMP2_Init(void)
{

  /* USER CODE BEGIN OPAMP2_Init 0 */

  /* USER CODE END OPAMP2_Init 0 */

  /* USER CODE BEGIN OPAMP2_Init 1 */

  /* USER CODE END OPAMP2_Init 1 */
  hopamp2.Instance = OPAMP2;
  hopamp2.Init.PowerMode = OPAMP_POWERMODE_NORMALSPEED;
  hopamp2.Init.Mode = OPAMP_PGA_MODE;
  hopamp2.Init.NonInvertingInput = OPAMP_NONINVERTINGINPUT_IO0;
  hopamp2.Init.InternalOutput = DISABLE;
  hopamp2.Init.TimerControlledMuxmode = OPAMP_TIMERCONTROLLEDMUXMODE_DISABLE;
  hopamp2.Init.PgaConnect = OPAMP_PGA_CONNECT_INVERTINGINPUT_IO0;
  hopamp2.Init.PgaGain = OPAMP_PGA_GAIN_16_OR_MINUS_15;
  hopamp2.Init.UserTrimming = OPAMP_TRIMMING_FACTORY;
  if (HAL_OPAMP_Init(&hopamp2) != HAL_OK)
  {
    Error_Handler();
  }
  /* USER CODE BEGIN OPAMP2_Init 2 */

  /* USER CODE END OPAMP2_Init 2 */

}
/* OPAMP3 init function */
void MX_OPAMP3_Init(void)
{

  /* USER CODE BEGIN OPAMP3_Init 0 */

  /* USER CODE END OPAMP3_Init 0 */

  /* USER CODE BEGIN OPAMP3_Init 1 */

  /* USER CODE END OPAMP3_Init 1 */
  hopamp3.Instance = OPAMP3;
  hopamp3.Init.PowerMode = OPAMP_POWERMODE_NORMALSPEED;
  hopamp3.Init.Mode = OPAMP_PGA_MODE;
  hopamp3.Init.NonInvertingInput = OPAMP_NONINVERTINGINPUT_IO0;
  hopamp3.Init.InternalOutput = DISABLE;
  hopamp3.Init.TimerControlledMuxmode = OPAMP_TIMERCONTROLLEDMUXMODE_DISABLE;
  hopamp3.Init.PgaConnect = OPAMP_PGA_CONNECT_INVERTINGINPUT_IO0;
  hopamp3.Init.PgaGain = OPAMP_PGA_GAIN_16_OR_MINUS_15;
  hopamp3.Init.UserTrimming = OPAMP_TRIMMING_FACTORY;
  if (HAL_OPAMP_Init(&hopamp3) != HAL_OK)
  {
    Error_Handler();
  }
  /* USER CODE BEGIN OPAMP3_Init 2 */

  /* USER CODE END OPAMP3_Init 2 */

}

void HAL_OPAMP_MspInit(OPAMP_HandleTypeDef* opampHandle)
{

  GPIO_InitTypeDef GPIO_InitStruct = {0};
  if(opampHandle->Instance==OPAMP1)
  {
  /* USER CODE BEGIN OPAMP1_MspInit 0 */

  /* USER CODE END OPAMP1_MspInit 0 */

    __HAL_RCC_GPIOA_CLK_ENABLE();
    /**OPAMP1 GPIO Configuration
    PA1     ------> OPAMP1_VINP
    PA2     ------> OPAMP1_VOUT
    PA3     ------> OPAMP1_VINM0
    */
    GPIO_InitStruct.Pin = GPIO_PIN_1|GPIO_PIN_2|GPIO_PIN_3;
    GPIO_InitStruct.Mode = GPIO_MODE_ANALOG;
    GPIO_InitStruct.Pull = GPIO_NOPULL;
    HAL_GPIO_Init(GPIOA, &GPIO_InitStruct);

  /* USER CODE BEGIN OPAMP1_MspInit 1 */

  /* USER CODE END OPAMP1_MspInit 1 */
  }
  else if(opampHandle->Instance==OPAMP2)
  {
  /* USER CODE BEGIN OPAMP2_MspInit 0 */

  /* USER CODE END OPAMP2_MspInit 0 */

    __HAL_RCC_GPIOA_CLK_ENABLE();
    /**OPAMP2 GPIO Configuration
    PA5     ------> OPAMP2_VINM0
    PA6     ------> OPAMP2_VOUT
    PA7     ------> OPAMP2_VINP
    */
    GPIO_InitStruct.Pin = GPIO_PIN_5|GPIO_PIN_6|GPIO_PIN_7;
    GPIO_InitStruct.Mode = GPIO_MODE_ANALOG;
    GPIO_InitStruct.Pull = GPIO_NOPULL;
    HAL_GPIO_Init(GPIOA, &GPIO_InitStruct);

  /* USER CODE BEGIN OPAMP2_MspInit 1 */

  /* USER CODE END OPAMP2_MspInit 1 */
  }
  else if(opampHandle->Instance==OPAMP3)
  {
  /* USER CODE BEGIN OPAMP3_MspInit 0 */

  /* USER CODE END OPAMP3_MspInit 0 */

    __HAL_RCC_GPIOB_CLK_ENABLE();
    /**OPAMP3 GPIO Configuration
    PB0     ------> OPAMP3_VINP
    PB1     ------> OPAMP3_VOUT
    PB2     ------> OPAMP3_VINM0
    */
    GPIO_InitStruct.Pin = GPIO_PIN_0|GPIO_PIN_1|GPIO_PIN_2;
    GPIO_InitStruct.Mode = GPIO_MODE_ANALOG;
    GPIO_InitStruct.Pull = GPIO_NOPULL;
    HAL_GPIO_Init(GPIOB, &GPIO_InitStruct);

  /* USER CODE BEGIN OPAMP3_MspInit 1 */

  /* USER CODE END OPAMP3_MspInit 1 */
  }
}

void HAL_OPAMP_MspDeInit(OPAMP_HandleTypeDef* opampHandle)
{

  if(opampHandle->Instance==OPAMP1)
  {
  /* USER CODE BEGIN OPAMP1_MspDeInit 0 */

  /* USER CODE END OPAMP1_MspDeInit 0 */

    /**OPAMP1 GPIO Configuration
    PA1     ------> OPAMP1_VINP
    PA2     ------> OPAMP1_VOUT
    PA3     ------> OPAMP1_VINM0
    */
    HAL_GPIO_DeInit(GPIOA, GPIO_PIN_1|GPIO_PIN_2|GPIO_PIN_3);

  /* USER CODE BEGIN OPAMP1_MspDeInit 1 */

  /* USER CODE END OPAMP1_MspDeInit 1 */
  }
  else if(opampHandle->Instance==OPAMP2)
  {
  /* USER CODE BEGIN OPAMP2_MspDeInit 0 */

  /* USER CODE END OPAMP2_MspDeInit 0 */

    /**OPAMP2 GPIO Configuration
    PA5     ------> OPAMP2_VINM0
    PA6     ------> OPAMP2_VOUT
    PA7     ------> OPAMP2_VINP
    */
    HAL_GPIO_DeInit(GPIOA, GPIO_PIN_5|GPIO_PIN_6|GPIO_PIN_7);

  /* USER CODE BEGIN OPAMP2_MspDeInit 1 */

  /* USER CODE END OPAMP2_MspDeInit 1 */
  }
  else if(opampHandle->Instance==OPAMP3)
  {
  /* USER CODE BEGIN OPAMP3_MspDeInit 0 */

  /* USER CODE END OPAMP3_MspDeInit 0 */

    /**OPAMP3 GPIO Configuration
    PB0     ------> OPAMP3_VINP
    PB1     ------> OPAMP3_VOUT
    PB2     ------> OPAMP3_VINM0
    */
    HAL_GPIO_DeInit(GPIOB, GPIO_PIN_0|GPIO_PIN_1|GPIO_PIN_2);

  /* USER CODE BEGIN OPAMP3_MspDeInit 1 */

  /* USER CODE END OPAMP3_MspDeInit 1 */
  }
}

/* USER CODE BEGIN 1 */

/* USER CODE END 1 */

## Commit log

2025-06-05 Add Hardware File
2025-06-05 Add Mech/Software/Readme
2025-06-06 Update README.md format
2025-06-06 Add href url
